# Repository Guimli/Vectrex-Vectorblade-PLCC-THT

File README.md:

# Vectrex-Vectorblade-PLCC-THT

PCB for VectorBlade with PLCC format memory on through-hole support.

I preferred to use a through-hole mount because it is more solid. And it has a hole on the bottom to eject the PLCC board easily without a puller.
The bracket is 8.1mm, which is only slightly more than the space between the PCB and the top of the plastic shell of the cartridge. I therefore recommend reducing the size of the bracket by removing the feet from the PLCC bracket.

This board is currently being tested and is not ready for production.

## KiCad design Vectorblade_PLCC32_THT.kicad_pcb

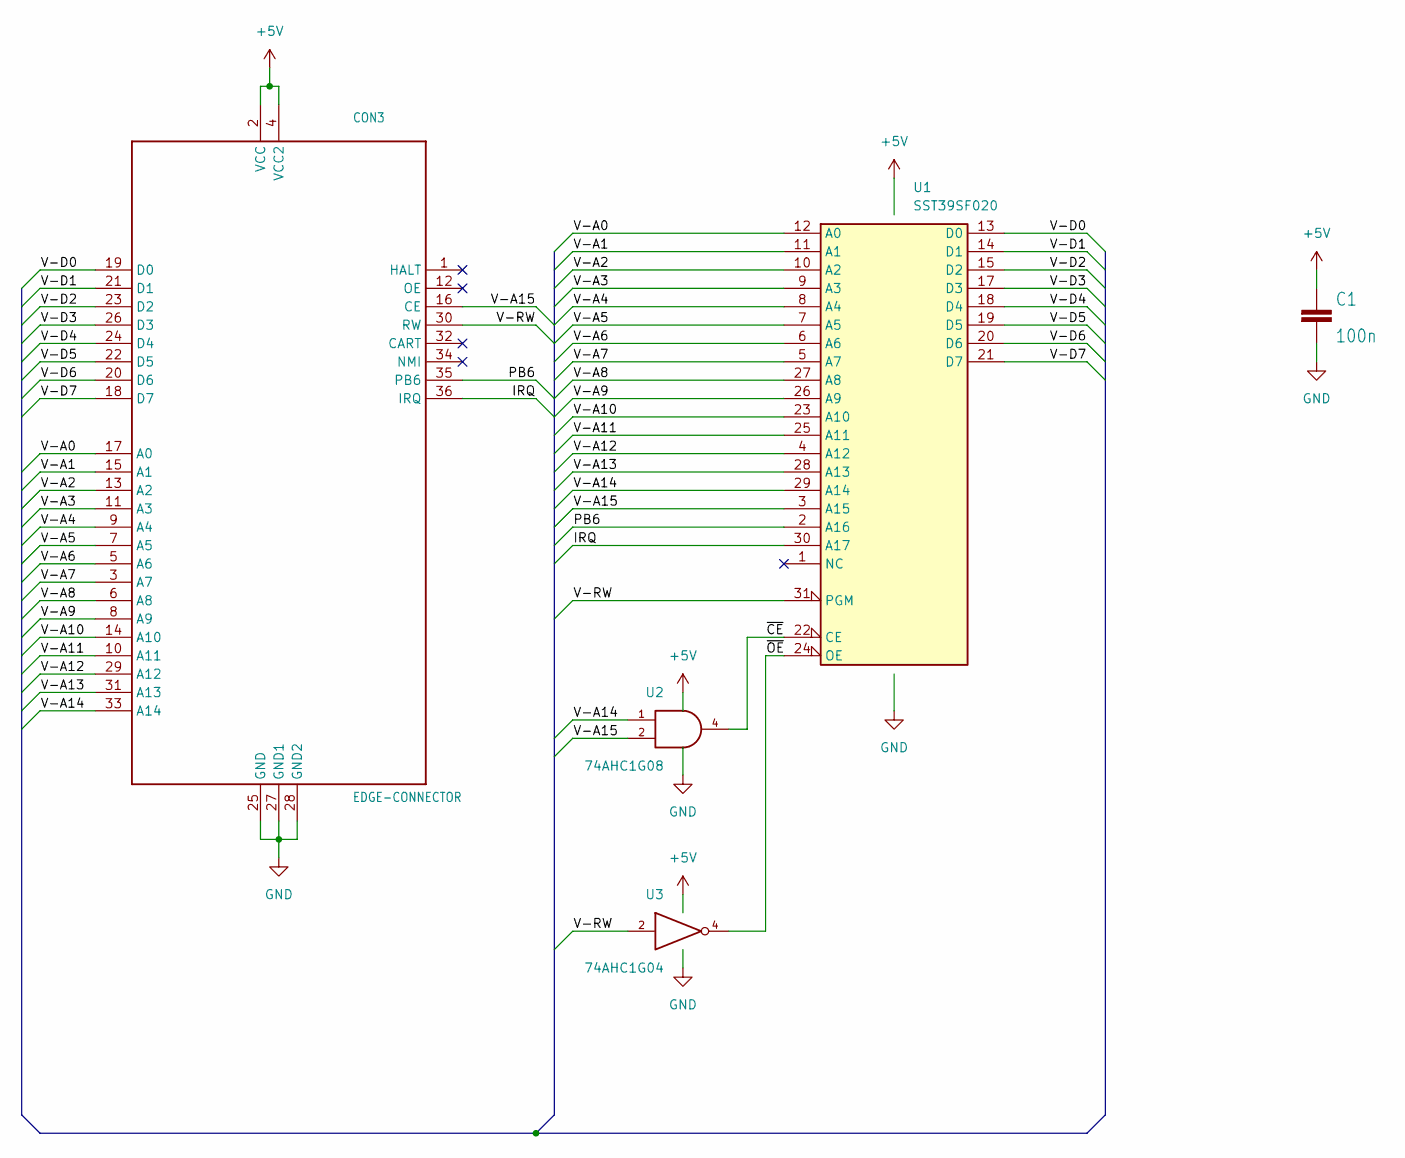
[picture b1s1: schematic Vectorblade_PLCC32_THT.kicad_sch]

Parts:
C1: 100n; C_0805_2012Metric
CON3: EDGE-CONNECTOR
U1: SST39SF020; PLCC-32_THT-Socket
U2: 74AHC1G08; SOT-23-5
U3: 74AHC1G04; SOT-23-5

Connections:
+5V: C1.1, CON3.2 (VCC), CON3.4 (VCC2), U1.32 (VCC), U2.5 (VCC), U3.5 (VCC)
/IRQ: CON3.36 (IRQ), U1.30 (A17)
/PB6: CON3.35 (PB6), U1.2 (A16)
/V-A0: CON3.17 (A0), U1.12 (A0)
/V-A1: CON3.15 (A1), U1.11 (A1)
/V-A2: CON3.13 (A2), U1.10 (A2)
/V-A3: CON3.11 (A3), U1.9 (A3)
/V-A4: CON3.9 (A4), U1.8 (A4)
/V-A5: CON3.7 (A5), U1.7 (A5)
/V-A6: CON3.5 (A6), U1.6 (A6)
/V-A7: CON3.3 (A7), U1.5 (A7)
/V-A8: CON3.6 (A8), U1.27 (A8)
/V-A9: CON3.8 (A9), U1.26 (A9)
/V-A10: CON3.14 (A10), U1.23 (A10)
/V-A11: CON3.10 (A11), U1.25 (A11)
/V-A12: CON3.29 (A12), U1.4 (A12)
/V-A13: CON3.31 (A13), U1.28 (A13)
/V-A14: CON3.33 (A14), U1.29 (A14), U2.1
/V-A15: CON3.16 (CE), U1.3 (A15), U2.2
/V-D0: CON3.19 (D0), U1.13 (D0)
/V-D1: CON3.21 (D1), U1.14 (D1)
/V-D2: CON3.23 (D2), U1.15 (D2)
/V-D3: CON3.26 (D3), U1.17 (D3)
/V-D4: CON3.24 (D4), U1.18 (D4)
/V-D5: CON3.22 (D5), U1.19 (D5)
/V-D6: CON3.20 (D6), U1.20 (D6)
/V-D7: CON3.18 (D7), U1.21 (D7)
/V-RW: CON3.30 (RW), U1.31 (PGM), U3.2
/~CE: U1.22 (CE), U2.4
/~OE: U1.24 (OE), U3.4
GND: C1.2, CON3.25 (GND), CON3.27 (GND1), CON3.28 (GND2), U1.16 (GND), U2.3 (GND), U3.3 (GND)

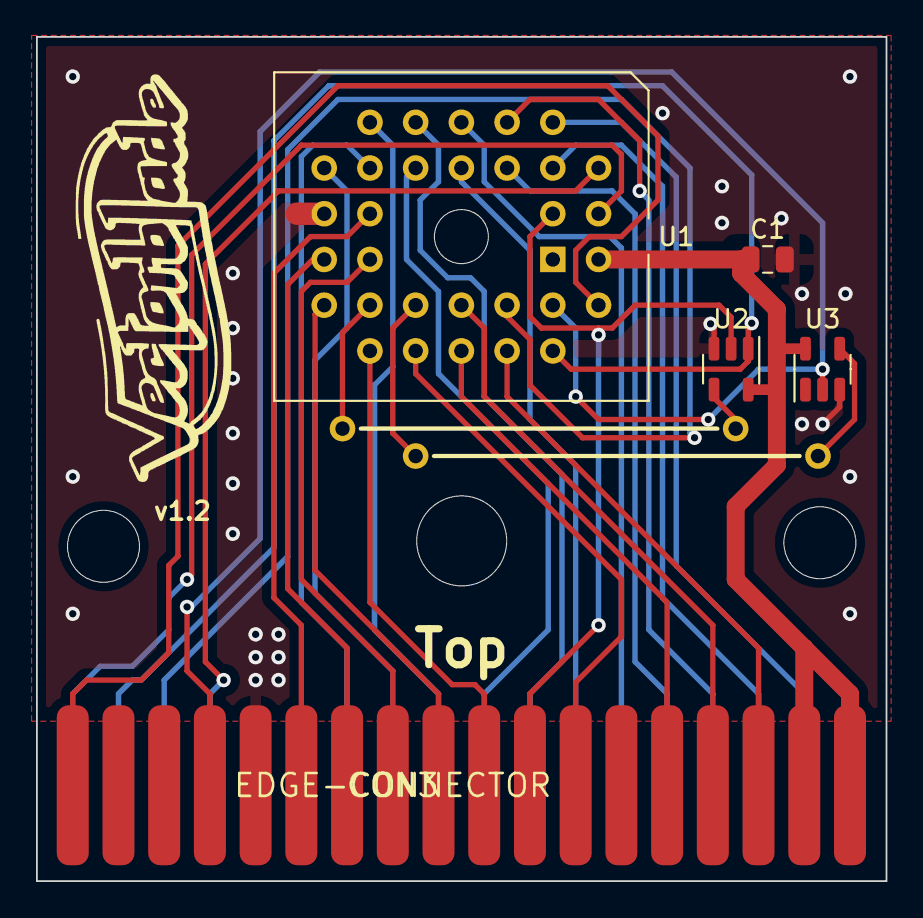
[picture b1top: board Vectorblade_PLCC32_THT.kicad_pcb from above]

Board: 2 copper layers, 47.2 x 46.9 mm, 8 parts (0 on the bottom side), 31 nets.

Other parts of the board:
@HOLE0, @HOLE1, @HOLE2: (no value)

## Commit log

2022-07-23 Esthetic
2022-10-18 Correct CE error
    Correct CE schematic and board error
2022-10-22 Correct a roud track
2022-11-27 I forgot to connect A15
    Shame !
2022-11-28 Remove Edge-Connector Silkscreen
2023-08-11 Update Gerber
